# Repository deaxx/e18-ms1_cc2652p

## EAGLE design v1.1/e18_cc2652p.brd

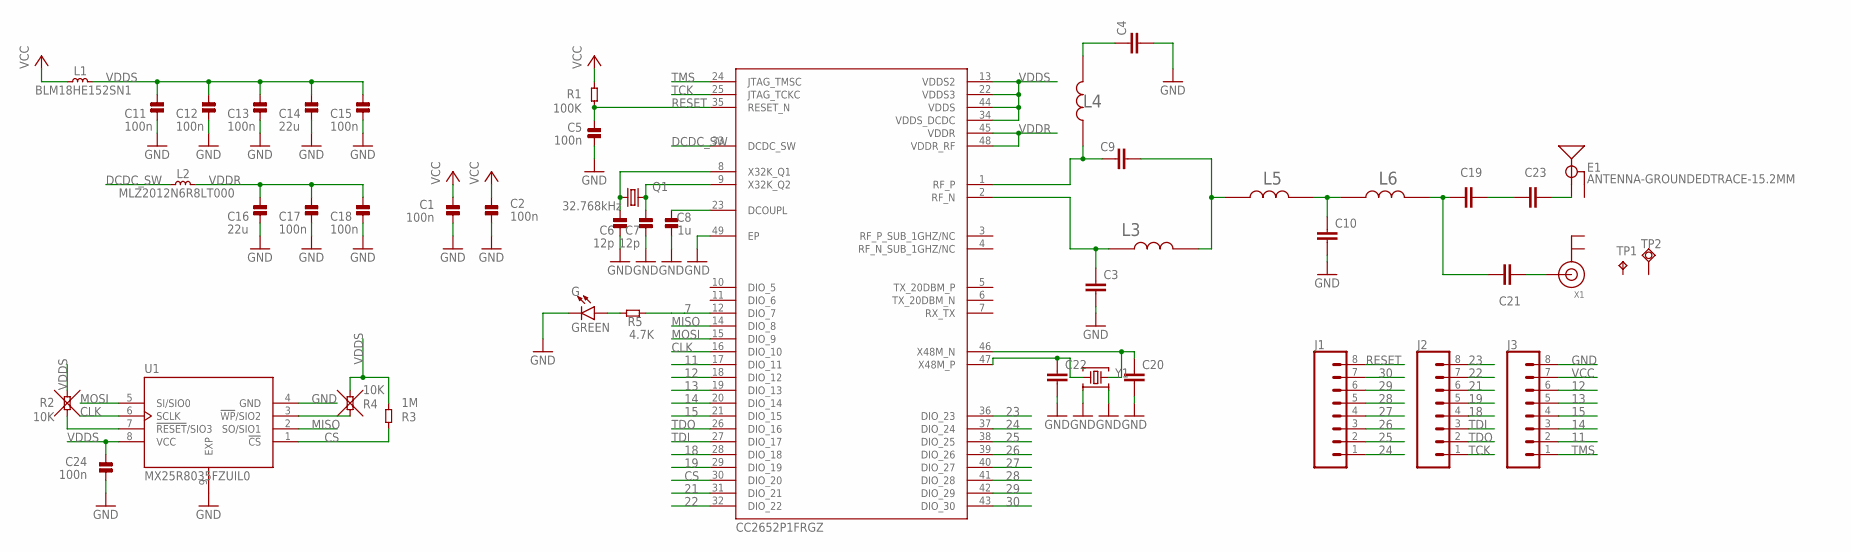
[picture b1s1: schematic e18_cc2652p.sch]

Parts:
C1, C2, C5, C11, C12, C13, C15, C17, C18, C24: 100n; _PKG_C_0402
C3, C9, C10: 1pf; CAPC1005X40N
C4, C19: 12pf; CAPC1005X40N
C6, C7: 12p; _PKG_C_0402
C8: 1u; _PKG_C_0402
C14, C16: 22u; _PKG_C_0805
C20, C22: 6.8pf; CAPC1005X40N
C21: 2.2pf; CAPC1005X40N
C23: 1.8pf; CAPC1005X40N
E1: ANTENNA-GROUNDEDTRACE-15.2MM; TRACE_ANTENNA_2.4GHZ_15.2MM
G: GREEN; LED-0603
IC3: CC2652P1FRGZ; RGZ0048A-MFG
J1, J2, J3: CONN_111X8-1.27MM; 1X11-1.27MM
L1: BLM18HE152SN1; _PKG_L_0603
L2: MLZ2012N6R8LT000; _PKG_C_0805
L3, L4: 2.4nH; INDC1005X40N
L5, L6: 2nH; INDC1005X40N
Q1: 32.768kHz; 2.0X1.2
R1: 100K; _PKG_C_0402
R2, R4: 10K; _PKG_C_0402
R3: 1M; _PKG_C_0402
R5: 4.7K; _PKG_C_0402
TP1: TPTP06SQ; TP05SQ
TP2: TPSQTP15SQ; TP15SQ
U1: MX25R8035FZUIL0; PSON50P200X300X60-9N
X1: ANTENNA_U.FL; U.FL
Y1: Q22FA12800150; XTAL-4P-2016

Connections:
7: IC3.12 (DIO_7), R5.1
11: IC3.17 (DIO_11), J3.2
12: IC3.18 (DIO_12), J3.6
13: IC3.19 (DIO_13), J3.5
14: IC3.20 (DIO_14), J3.3
15: IC3.21 (DIO_15), J3.4
18: IC3.28 (DIO_18), J2.4
19: IC3.29 (DIO_19), J2.5
21: IC3.31 (DIO_21), J2.6
22: IC3.32 (DIO_22), J2.7
23: IC3.36 (DIO_23), J2.8
24: IC3.37 (DIO_24), J1.1
25: IC3.38 (DIO_25), J1.2
26: IC3.39 (DIO_26), J1.3
27: IC3.40 (DIO_27), J1.4
28: IC3.41 (DIO_28), J1.5
29: IC3.42 (DIO_29), J1.6
30: IC3.43 (DIO_30), J1.7
CLK: IC3.16 (DIO_10), U1.6 (SCLK)
CS: IC3.30 (DIO_20), R3.2, U1.1 (!CS)
DCDC_SW: IC3.33 (DCDC_SW), L2.1
GND: C1.1, C2.1, C3.2, C4.2, C5.1, C6.1, C7.1, C8.1, C10.2, C11.2, C12.2, C13.2, C14.2, C15.2, C16.2, C17.2, C18.2, C20.2, C22.2, C24.1, G.C, IC3.49 (EP), J3.8, U1.4 (GND), U1.9 (EXP), Y1.2, Y1.4
MISO: IC3.14 (DIO_8), U1.2 (SO/SIO1)
MOSI: IC3.15 (DIO_9), U1.5 (SI/SIO0)
unnamed: C9.1, IC3.1 (RF_P), L4.1
unnamed: C3.1, IC3.2 (RF_N), L3.1
unnamed: C4.1, L4.2
unnamed: C9.2, L3.2, L5.1
unnamed: C19.1, C21.1, L6.2
unnamed: C21.2, X1.3 (SIGNAL)
unnamed: C19.2, C23.1
unnamed: C23.2, E1.ANT (SIGNAL)
unnamed: C8.2, IC3.23 (DCOUPL)
unnamed: C10.1, L5.2, L6.1
unnamed: R2.1, U1.7 (!RESET!/SIO3)
unnamed: C20.1, IC3.46 (X48M_N), Y1.3
unnamed: R4.2, U1.3 (!WP!/SIO2)
unnamed: G.A, R5.2
unnamed: C22.1, IC3.47 (X48M_P), Y1.1
RESET: C5.2, IC3.35 (RESET_N), J1.8, R1.1
TCK: IC3.25 (JTAG_TCKC), J2.1
TDI: IC3.27 (DIO_17), J2.3
TDO: IC3.26 (DIO_16), J2.2
TMS: IC3.24 (JTAG_TMSC), J3.1
VCC: C1.2, C2.2, J3.7, L1.1, R1.2
VDDR: C16.1, C17.1, C18.1, IC3.45 (VDDR), IC3.48 (VDDR_RF), L2.2
VDDS: C11.1, C12.1, C13.1, C14.1, C15.1, C24.2, IC3.13 (VDDS2), IC3.22 (VDDS3), IC3.34 (VDDS_DCDC), IC3.44 (VDDS), L1.2, R2.2, R3.1, R4.1, U1.8 (VCC)
X32K_Q1: C6.2, IC3.8 (X32K_Q1), Q1.1
X32K_Q2: C7.2, IC3.9 (X32K_Q2), Q1.2

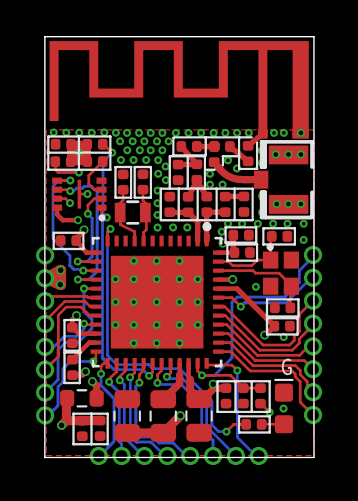
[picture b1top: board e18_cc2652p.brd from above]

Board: 4 copper layers, 14.9 x 23.4 mm, 47 parts (0 on the bottom side), 49 nets.

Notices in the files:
parts and their libraries:
SparkFun-RF2: Licensing: Creative Commons ShareAlike 4.0 International - https://creativecommons.org/licenses/by-sa/4.0
CC2652P1FRGZR: COPYRIGHT: Copyright (C) 2022 Ultra Librarian. All rights reserved.
crystal-geyer_V1_0: Copyright: Geyer-Electronic
